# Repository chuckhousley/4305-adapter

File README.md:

The THAT 4301 is out of production and hard to find so I downloaded KiCad and learned how to make this. The values below were not prototyped or iterated in any way I just followed the transition guide from THAT corp. Short demo here: https://www.youtube.com/watch?v=3GVIXIjW9iY 

* BOM

| Reference | Value                            |
| ----------|--------------------------------- |
| R1        | 5k1                              |
| R2        | 6k2                              |
| C1        | 220p                             |
| U1        | THAT4305                         |
| U2, U3    | NJM8080 (or any dual op amp idk) |

* License
CC BY 4.0

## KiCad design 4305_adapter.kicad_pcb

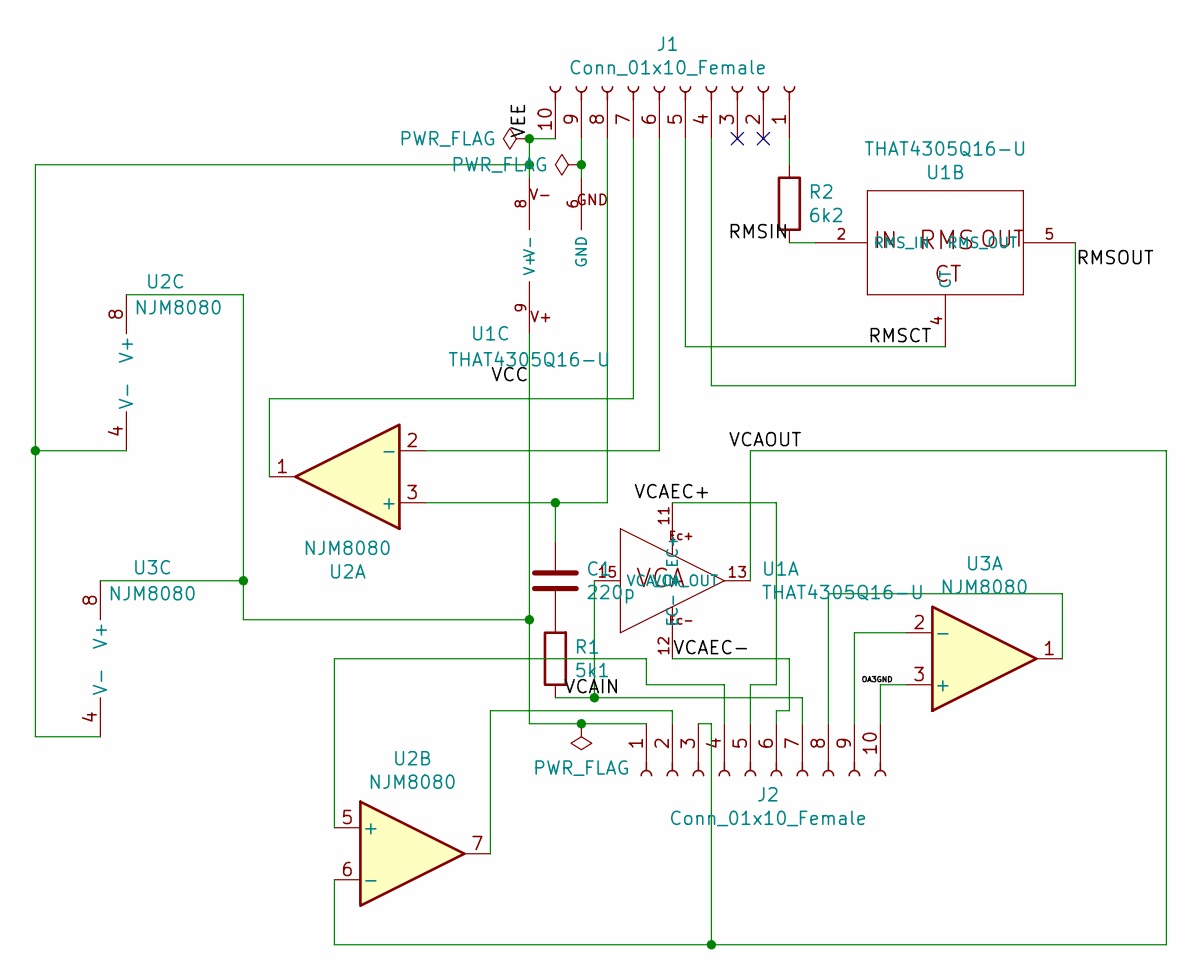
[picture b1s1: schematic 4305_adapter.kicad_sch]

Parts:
C1: 220p; C_Rect_L4.0mm_W2.5mm_P2.50mm
J1, J2: Conn_01x10_Female; 1X10_LOCK_LONGPADS
R1: 5k1; R_Axial_DIN0207_L6.3mm_D2.5mm_P10.16mm_Horizontal
R2: 6k2; R_Axial_DIN0207_L6.3mm_D2.5mm_P10.16mm_Horizontal
U1: THAT4305Q16-U; QSOP-16_3.9x4.9mm_P0.635mm
U2, U3: NJM8080; SOP-8_3.9x4.9mm_P1.27mm

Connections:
/OA3GND: J2.10, U3.3 (+)
/RMSCT: J1.5, U1.4 (CT)
/RMSIN: R2.2, U1.2 (RMS_IN)
/RMSOUT: J1.4, U1.5 (RMS_OUT)
/VCAEC+: J2.5, U1.11 (EC+)
/VCAEC-: J2.6, U1.12 (EC-)
/VCAIN: J2.7, R1.1, U1.15 (VCA_IN)
/VCAOUT: J2.3, U1.13 (VCA_OUT), U2.6 (-)
/VCC: J2.1, U1.9 (V+), U2.8 (V+), U3.8 (V+)
/VEE: J1.10, U1.8 (V-), U2.4 (V-), U3.4 (V-)
unnamed: C1.1, J1.8, U2.3 (+)
unnamed: C1.2, R1.2
unnamed: J1.1, R2.1
unnamed: J1.6, U2.2 (-)
unnamed: J1.7, U2.1
unnamed: J1.9, U1.6 (GND)
unnamed: J2.2, U2.7
unnamed: J2.4, U2.5 (+)
unnamed: J2.8, U3.1
unnamed: J2.9, U3.2 (-)

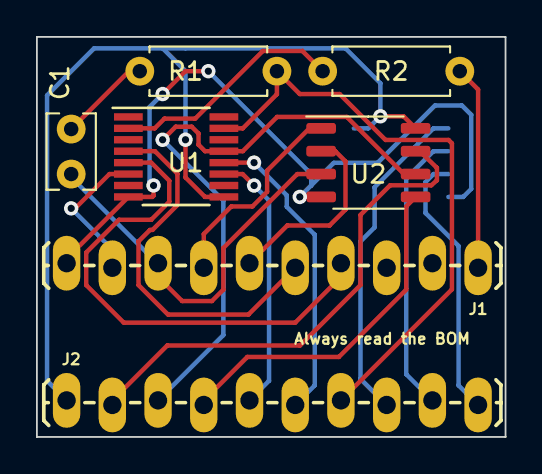
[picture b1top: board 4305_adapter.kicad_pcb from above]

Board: 2 copper layers, 26.0 x 22.2 mm, 8 parts (1 on the bottom side), 20 nets.

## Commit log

2020-08-16 init
2020-08-16 Fix table
